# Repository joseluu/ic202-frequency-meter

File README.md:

# Fréquencemètre IC-202

Projet KiCad transcrit du schéma manuscrit, selon la description de
`docs/specifications.md`. Deux versions du schéma existent dans `docs/` :
`Schema.jpg`, la première photo, et `Schema_propre.jpg`, une reprise plus
lisible qui a servi à corriger plusieurs valeurs mal lues sur la première.

Chaîne de mesure : entrée RF → prédiviseur MB506 → étage de mise en forme à
transistor alimenté en 3 V → broche D5 d'un Arduino Pro Mini → afficheur LCD
3 digits 7 segments multiplexé, déporté au bout d'une nappe.

## Contenu

| Fichier | Rôle |
|---|---|
| `kicad/ic202-frequencemetre.kicad_pro` | Projet KiCad 10 |
| `kicad/ic202-frequencemetre.kicad_sch` | Schéma (feuille A3 unique) |
| `kicad/ic202-frequencemetre.kicad_pcb` | Carte, encore vide |
| `kicad/IC202.kicad_sym` | Symboles créés pour ce projet |
| `kicad/sym-lib-table` | Enregistrement de la bibliothèque de symboles `IC202` (portée projet) |
| `kicad/frequencemetre.pretty/` | Empreintes créées pour ce projet |
| `kicad/fp-lib-table` | Enregistrement de la bibliothèque d'empreintes `frequencemetre` (portée projet) |
| `kicad/ic202-frequencemetre.pdf` / `.svg` | Schéma exporté |
| `kicad/bom.csv` | Nomenclature |
| `kicad/erc.rpt` | Rapport ERC |
| `docs/Schema.jpg`, `docs/Schema_propre.jpg` | Schéma manuscrit d'origine et sa reprise lisible |
| `docs/LCD.png` | Fiche technique de l'afficheur LCD |

## État de vérification

- ERC : **0 erreur, 0 avertissement**.
- Netlist vérifiée broche à broche par export `kicadxml` après chaque retouche.
- `check_label_rotations.py` et `check_symbol_overlap.py` : OK.
- `lint_offgrid` : aucune coordonnée hors grille 1,27 mm.

## Organisation du schéma

La disposition reprend celle du schéma papier : alimentation en bandeau haut,
prédiviseur à gauche, mise en forme au centre, Arduino à droite, afficheur en
bas à droite. Les liaisons courtes à l'intérieur d'un bloc sont des fils ; les
rails d'alimentation et les signaux entre blocs passent par étiquettes de net.

## Règles de lisibilité appliquées

Les directives du skill
[kicad-schematic-readability](https://github.com/joseluu/kicad-schematic-readability)
sont respectées, et vérifiées par deux scripts locaux au poste de travail :

```
python check_label_rotations.py  .../ic202-frequencemetre.kicad_sch   # OK
python check_symbol_overlap.py   .../ic202-frequencemetre.kicad_sch   # OK
```

- **GND indépendants** : aucun fil de masse ne traverse la feuille, chaque
  composant a son propre stub GND.
- **Alimentation en haut, GND en bas** : les découplages ont leur broche
  positive vers le haut et leur masse vers le bas. Les connecteurs suivent la
  même règle : `J1` porte le +12 V en haut et la masse en bas, `J2` a son
  blindage dirigé vers le bas. Les deux ont été retournés par un miroir, ce qui
  inverse l'ordre des broches sans déplacer la broche de signal.
- **Signaux de gauche à droite** : entrée RF à gauche, progression vers
  l'Arduino puis l'afficheur à droite.
- **Étiquettes réservées aux signaux utiles** : rails, RF_IN, D5_SIG,
  VLCD_MID et les dix lignes LCD_COM/LCD_SEG. SW1 et SW2 sont marquées non
  connectées plutôt qu'étiquetées, faute d'utilité une fois flottantes.
- **Aucun chevauchement de symboles.**

### Placement des repères et valeurs

- **Circuits intégrés rectangulaires** (`U1`, `U2`, `U3`, `A1`, `DS1`) : repère
  et valeur au centre du rectangle, l'intérieur étant libre depuis le masquage
  des noms de broches. Ces champs ne portent aucun `justify`, le défaut centré
  étant celui recherché.
- **Résistances** : valeur au centre du corps et repère sur la ligne au-dessus,
  les deux suivant l'orientation du composant. Pour une résistance verticale le
  texte se lit de bas en haut, donc la ligne au-dessus est celle de gauche.
- **Condensateurs** : repère et valeur de part et d'autre du fil du symbole,
  juste sous les armatures. Le cas vertical exige un `justify` explicite, sinon
  le texte traverse le fil. Le cas horizontal sépare par la hauteur.

### Convention d'orientation des étiquettes

Une étiquette de net a besoin des **deux** informations, et elles doivent être
cohérentes entre elles :

- l'**angle** donne l'axe de lecture, et sert d'indicateur de direction pour le
  script de contrôle ;
- le **`justify`** décide de quel côté du point d'ancrage le texte est posé.
  C'est lui seul que KiCad utilise pour placer le texte.

| Angle | `justify` | Le texte se pose |
|---|---|---|
| 0 | `left bottom` | à droite de l'ancrage |
| 90 | `left bottom` | au-dessus |
| 180 | `right bottom` | à gauche |
| 270 | `right bottom` | en dessous |

Le second mot `bottom` décale le texte perpendiculairement, pour qu'il ne soit
pas posé sur le fil.

**Piège n° 1 : pas de `justify` du tout.** Le défaut de KiCad est *centré*, donc
l'étiquette chevauche son propre point de connexion et le numéro de broche.
C'est visible surtout sur les étiquettes posées directement sur une broche, les
étiquettes en bout de stub ayant de la place autour. Chaque étiquette doit
porter un `justify` explicite.

**Piège n° 2 : `lint_schematic_cosmetic` passe `orient_labels`.** Cette passe du
serveur MCP produit une orientation à 180° de la bonne. Ne pas la relancer sur
ce schéma. Si c'est fait par erreur, réappliquer la table ci-dessus.

**Autre piège.** Dans un champ `property` d'un symbole tourné à 90°, l'angle
est relatif au symbole : il faut écrire 270 pour obtenir un texte horizontal.
C'est le cas des repères de `R7`..`R16`.

### Alimentation

`J1` (+12 V) → `U1` AMS1117-5.0 → +5 V → `U2` AMS1117 (ADJ) → +3 V.
Découplage 100 nF + 10 µF sur chacun des trois rails.

Les deux régulateurs sont en boîtier CMS SOT-223, choisis dans le stock
PartsBox de l'utilisateur plutôt que les L7805/LM317L d'origine (traversants,
non tenus en stock CMS) : mêmes coordonnées de broches, seule leur
numérotation change. Sur `U1`, l'entrée devient la broche 3 (VI) et la
sortie la broche 2 (VO) — sur `U2`, `1`=ADJ, `2`=VO, `3`=VI comme
auparavant, l'architecture (référence 1,25 V, pont diviseur) étant la même
famille que le LM317.

Le +3 V est réglé par `R1` (220 R, VO→ADJ de `U2`) et `R2` (300 R,
ADJ→GND) :

    Vout = 1,25 x (1 + 300/220) = 2,95 V

C'est proche de la tension de service du LCD (3,0 V), indiquée sur sa fiche.
Ce pont n'a pas changé de valeur : l'AMS1117 ajustable utilise la même
référence 1,25 V que le LM317L qu'il remplace.

`#FLG01` et `#FLG02` sont les PWR_FLAG des rails +12 V et GND, qui ne sont
alimentés que par un connecteur.

`J1` est un connecteur 4 broches (header 2,54 mm) : les broches 1 et 2,
adjacentes, portent toutes deux le +12 V ; les broches 3 et 4, adjacentes,
portent toutes deux le GND. Le doublement de chaque broche répartit le
courant d'alimentation sur deux points de contact.

### Prédiviseur MB506

`U3` est le Fujitsu **MB506PF**, boîtier CMS SOP-8 (208 mil, empreinte
`Package_SO:SOIC-8_5.3x6.2mm_P1.27mm`), en remplacement du MB506 traversant
DIP-8 d'origine — même brochage 1-8 (IN, VCC, SW1, OUT, GND, SW2, NC, /IN),
choisi dans le stock PartsBox de l'utilisateur.

- `J2` entrée RF, terminaison `R3` 51 R, liaison capacitive `C7` 1 nF vers IN (broche 1).
  Pas de connecteur SMA monté : un mini câble coaxial est soudé directement
  sur deux pastilles (`TestPoint:TestPoint_2Pads_Pitch2.54mm_Drill0.8mm`,
  pas 2,54 mm, perçage 0,8 mm) — âme sur la pastille 1 (IN), blindage sur
  la pastille 2 (GND).
- Entrée complémentaire /IN (broche 8) : découplée à la masse par `C8` 100 nF,
  et polarisée par `R20` 470 kΩ vers GND. C'est le réseau optionnel repéré sur
  le schéma relu (voir « Hypothèses de transcription ») ; il fixe le point de
  repos de l'entrée complémentaire quand le MB506 est piloté en simple
  extrémité (un seul signal sur IN, ~IN laissée au repos).
- VCC (broche 2) en +5 V, découplé par `C9` 100 nF.
- Sortie OUT (broche 4) : pull-down `R19` (2K2) vers GND, en parallèle de la
  liaison capacitive vers l'étage de mise en forme. C'est une terminaison
  usuelle pour une sortie de type collecteur ouvert / ECL.
- Broche 7 (NC) marquée non connectée. La datasheet Fujitsu ne lui donne
  aucune fonction : le rapport de division est fixé uniquement par SW1 et
  SW2, il n'y a pas de troisième entrée de sélection.
- SW1 (broche 3) et SW2 (broche 6) reliées au rail +5 V **à travers un
  cavalier à souder fermé** (`JP11` sur `MB506_SW1`, `JP12` sur `MB506_SW2`,
  empreinte `Jumper:SolderJumper-2_P1.3mm_Bridged_Pad1.0x1.5mm`).

D'après la table du constructeur (H = VCC, L = ouvert), SW1 et SW2 au niveau H
donnent le rapport **1/64**, comportement par défaut de cette carte :

| SW1 | SW2 | Division |
|---|---|---|
| ouvert | ouvert | 1/256 |
| ouvert | +5 V | 1/128 |
| +5 V | ouvert | 1/128 |
| **+5 V** | **+5 V** | **1/64** |

Le schéma d'origine prévoyait un connecteur `J3` pour choisir le rapport ; il
n'apparaît plus sur le schéma relu, qui laisse SW1/SW2 flottants (1/256 par
défaut). À la demande explicite, les deux broches sont ici reliées au +5 V
pour fixer la division à 1/64. `JP11`/`JP12` remplacent ce sélecteur : livrés
fermés, ils conservent le 1/64 ; couper `JP11` **ou** `JP12` au cutter remet
la broche correspondante en l'air (niveau L) et donne 1/128, couper les deux
donne 1/256. Un coup de fer à souder revient en arrière.

### Mise en forme vers D5

`Q1` est le NPN RF **2SC5551AE-TD-E** (onsemi), boîtier CMS SOT-89
(30 V, 300 mA, fT = 3,5 GHz), en remplacement du 2N2369 traversant (TO-18,
fT ≈ 500 MHz) — choisi dans le stock PartsBox de l'utilisateur, largement
assez rapide pour ce rôle. Le brochage réel (1 = base, 2 = collecteur sur
la languette, 3 = émetteur) ne correspond pas à l'ordre du symbole générique
KiCad `Q_NPN_BEC` (broche 2 = émetteur, broche 3 = collecteur) : le symbole a
donc été remplacé par `Q_NPN_BCE` (broche 2 = collecteur, broche 3 =
émetteur), qui a la même géométrie de broches — seul l'étiquetage
broche/fonction change, le câblage existant reste intact — pour que la
numérotation corresponde à celle de l'empreinte SOT-89.

Sortie ECL du MB506 → `C10` 100 nF → base de `Q1`. `R4` 3,3 kΩ relie
la base au collecteur (contre-réaction continue, pas une résistance série vers
la masse comme dans une première version du schéma). Émetteur à la masse,
collecteur tiré au +3 V par `R6` 470 Ω, et c'est ce nœud collecteur qui attaque
D5. Le point de repos de `Q1` s'auto-régule par cette contre-réaction plutôt
que par un pont de base classique. Le niveau logique vu par l'Arduino est donc
bien du 3 V, d'où la présence du second régulateur (`U2`).

### Arduino

L'Arduino Pro Mini est la version **3,3 V / 8 MHz**, alimentée sur sa broche VCC
depuis le rail +3 V (le régulateur de la carte est contourné, RAW non connectée).
L'ATmega328P à 8 MHz fonctionne sans réserve jusqu'à 2,7 V.

D13 est laissé libre à cause de la LED intégrée. TXO/RXI restent disponibles
pour la programmation par le connecteur FTDI de la carte.

**Montage sur picots.** Le Pro Mini n'est pas soudé directement : il se
branche sur deux barrettes de picots femelles soudées sur le PCB principal
(empreinte `frequencemetre:Arduino_Pro_Mini_Header_2x12`). Il se trouve donc surélevé
par rapport à la carte, et le volume dégagé en dessous est disponible pour
d'autres composants. Cette empreinte ne modélise que les deux courtyards des
barrettes (pas de contour de carte complet ni de courtyard unique englobant
tout le module), justement pour ne pas signaler ce volume comme occupé.

Géométrie vérifiée contre l'empreinte open source
[`Arduino_Pro_Mini_Socket`](https://github.com/Alarm-Siren/arduino-kicad-library)
(2 rangées de 12 broches au pas de 2,54 mm, 15,24 mm entre rangées) : 24
broches au total, pas de connecteur de programmation FTDI modélisé. Les
broches A4/SDA et A5/SCL du Pro Mini réel ne sont pas sur ces barrettes — ce
sont des pastilles au dos du module, atteignables seulement par un fil volant
— et ont été retirées du symbole `IC202:Arduino_Pro_Mini`, qui ne comptait
d'ailleurs déjà aucune connexion sur ces deux broches.

### Afficheur LCD

`docs/LCD.png` donne la fiche du composant :

| Caractéristique | Valeur |
|---|---|
| Technologie | TN, polariseur réflectif positif |
| Multiplexage | 1/4 duty, 1/2 bias |
| Tension de service | 3,0 V |
| Angle de lecture | 6 heures |
| Broches | 10, au pas de 2,00 mm |

Référence commerciale :
<https://fr.aliexpress.com/item/1005003745628043.html>

Le 1/4 duty impose **4 communs**, et les 10 broches se répartissent donc en
4 communs plus **6 segments**. Cela adresse 4 × 6 = 24 segments, dont 21 pour
les trois chiffres.

C'est un afficheur à cristaux liquides : il ne consomme aucun courant et ne
supporte pas de tension continue permanente, qui le détruirait par
électrolyse. Il n'y a donc **pas de résistance de limitation** ; l'attaque se
fait en alternatif, par inversion de polarité à chaque trame.

**Attaque en 1/2 bias par tri-état.** Chaque ligne a besoin de trois niveaux :
0 V, 1,5 V et 3 V. Les broches de l'Arduino en fournissent deux, et le
troisième vient de la mise en haute impédance : la ligne rejoint alors la
référence à mi-tension `VLCD_MID` à travers sa résistance de 100 kΩ.

| Élément | Rôle |
|---|---|
| `R7`..`R16` (100 kΩ) | une par ligne, vers `VLCD_MID` |
| `R17`, `R18` (10 kΩ) | pont générant `VLCD_MID` = 3 V / 2 |
| `C12` (1 µF) | découplage de la référence |

Le pont est dix fois plus raide que les résistances de ligne, pour que la
référence ne bouge pas quand plusieurs broches commutent.

**Cavaliers de coupure devant `J4`.** Un cavalier à souder fermé par défaut
(`JP1`..`JP10`, empreinte `Jumper:SolderJumper-2_P1.3mm_Bridged_Pad1.0x1.5mm`)
est inséré en série entre chaque ligne (`R7`..`R16`) et sa broche de `J4` —
un par ligne LCD. Chaque ligne passe donc par deux nœuds électriques
distincts : le nœud côté Arduino/résistance (nom de net inchangé,
`LCD_COM1`..`LCD_SEG6`) et le nœud côté `J4` (nommé explicitement
`J4_COM1`..`J4_SEG6`), reliés par le cavalier. Fermés (comportement par
défaut, pont de cuivre déjà présent sur l'empreinte), la liaison vers la
nappe LCD est normale ; les couper au cutter isole la carte de la nappe —
utile pour tester l'étage Arduino/résistances seul avant de raccorder
l'afficheur. Un coup de fer à souder rétablit ensuite la liaison.

**Deux bugs de câblage trouvés et corrigés après coup, à l'occasion d'une
tentative de routage** (voir plus bas) :

1. Les 10 fils reliant chaque cavalier à sa broche de `J4` passaient par un
   point de coude intermédiaire à une abscisse commune (`x=330.2`) pour
   rester orthogonaux. Plusieurs de ces segments verticaux se chevauchaient
   partiellement sur cette même abscisse (les nappes de lignes LCD ont des
   pas différents côté résistances — 5,08 mm — et côté `J4` — 2,54 mm — donc
   leurs coudes intermédiaires ne tombent pas aux mêmes hauteurs), ce qui a
   **court-circuité entre elles plusieurs lignes LCD** (`COM2`-`COM3`-`COM4`-`SEG1`
   d'un côté, `SEG3`-`SEG4` de l'autre). L'ERC ne signalait qu'un avertissement
   discret (« multiple_net_names »), pas une erreur — c'est une relecture du
   netlist exporté par `kicad-cli` (source de vérité) qui a révélé l'ampleur
   réelle du problème. Corrigé en remplaçant les 10 chemins coudés par un
   fil diagonal unique par ligne (pas de point partagé entre lignes
   différentes, donc aucun risque de chevauchement accidentel).
2. Après correction du point 1, le nom de net explicite (`J4_COM1` etc.) a
   dû être ajouté sur chaque broche de `J4` : sans lui, `sync_schematic_to_board`
   (l'outil MCP qui importe le schéma dans le PCB) n'arrivait pas à
   résoudre les nets anonymes auto-générés par KiCad (`Net-(J4-Pin_X)`) et
   laissait ces broches et celles des cavaliers **sans net du tout** côté
   PCB — invisibles pour le ratsnest et l'autorouteur, silencieusement, sans
   qu'aucun outil ne le signale comme une erreur. Un nom de net explicite
   sur chaque broche contourne cette limite.

**Affectation des broches de l'Arduino :**

| Broche | Ligne LCD |
|---|---|
| D5 | entrée de comptage depuis l'étage transistor |
| D2, D3, D4, D6 | COM1, COM2, COM3, COM4 |
| D7, D8, D9, D10, D11, D12 | SEG1 à SEG6 |

**Liaison par nappe.** Le LCD est déporté au bout d'une nappe de 10
conducteurs. `J4` (header mâle au pas de 2,54 mm) est le seul connecteur
présent sur la carte ; `DS1`, l'afficheur, n'est **pas monté sur ce PCB**,
il se trouve à l'autre extrémité du câble. Le symbole `DS1` est marqué
« hors carte » (`on_board: no`) : il reste dans le schéma et la nomenclature
pour documenter le système complet, mais `sync_schematic_to_board` ne lui
crée pas d'empreinte sur cette carte.

## Intention de conception pour le placement/routage

Le schéma porte, en plus de la connectivité, une propriété masquée
`Placement` sur chaque composant dont la position physique finale importe
au-delà du simple raccordement électrique — suivant le skill Claude Code
`conception-electronique-kicad`. Cette propriété n'apparaît pas sur le
schéma ; elle se lit via `get_schematic_component` ou en filtrant le
`.kicad_sch` sur `(property "Placement"`. **Elle ne s'applique pas toute
seule** : au moment du placement/routage, il faut demander explicitement de
la respecter.

**Découplage documenté** (préfixe `LOCAL`) :

| Réf. | Rôle |
|---|---|
| `C1`, `C2` | HF / bulk BF, entrée `J1` et broche 3 (VI) de `U1` |
| `C3`, `C4` | HF / bulk BF, nœud +5 V partagé broche 2 (VO) de `U1` / broche 3 (VI) de `U2` |
| `C5`, `C6` | HF / bulk BF, broche VO (sortie) de `U2` |
| `C9` | HF, broche VCC de `U3` |
| `C8` | HF de la broche ~IN (signal, pas alimentation) de `U3`, avec `R20` |
| `C11` | HF du rail +3 V près de `R6`, point le plus éloigné de `U2` |
| `C12` | référence `VLCD_MID`, point milieu du pont `R17`/`R18` |

Vérification faite : les trois circuits intégrés actifs (`U1`, `U2`, `U3`)
ont chacun un découplage local documenté sur leur(s) broche(s)
d'alimentation. `A1` (Arduino Pro Mini) n'est pas inclus dans cette
vérification : c'est un module complet avec son propre découplage embarqué,
pas un CI nu à décrire ici.

**Boucles critiques documentées** (préfixe `LOOP CRITIQUE`, hors
découplage) :

- `J2`-`R3`-`C7` → broche IN de `U3` : chemin RF d'entrée, jusqu'à 2,4 GHz,
  surface minimale impérative.
- `U3`(OUT)-`R19`-`C10`-`R4`-`R6`-`Q1` → `D5_SIG` (broche D5 de `A1`) : chemin
  de comptage, le signal que l'instrument existe pour mesurer — à éloigner
  des sources de bruit.

### Placement initial (fait)

Carte **80 × 50 mm**, paysage (hauteur réduite de 70 à 50 mm après le
passage aux boîtiers CMS ci-dessous, qui a libéré de la place). Emplacements
imposés par l'utilisateur :

- `J1` (+12 V IN) : bord haut, au milieu, rangée de broches **parallèle**
  au bord (rotation 90° par rapport à l'orientation par défaut du
  footprint, qui les mettait perpendiculaires).
- `J2` (RF IN, coax à souder) : bord gauche, rangée de broches parallèle au
  bord (même correction de rotation).
- `J4` (nappe LCD, header 2,54 mm) : bord droit.
- `A1` (Arduino Pro Mini sur picots) : décalé de 3 mm vers la gauche par
  rapport au premier placement, toujours à droite et proche de `J4`,
  orientation paysage, extrémité USB/FTDI côté gauche (rotation 90°, vérifiée
  par la mesure des pads comme au premier placement).
- `R7`..`R16` (échelle de polarisation LCD) : **sous `A1`**, dans le volume
  dégagé entre les deux barrettes de picots — l'empreinte de `A1` ne porte
  que les deux courtyards des barrettes (voir « Arduino » ci-dessus), donc
  cet espace n'est pas signalé occupé.

L'orientation « parallèle au bord le plus proche » pour `J1`/`J2` est
désormais une règle par défaut du skill `kicad-pcb-placement` : elle
s'applique à tout connecteur proche d'un bord, sauf orientation contraire
explicitement demandée.

Le reste (bloc d'alimentation, chaîne RF/prédiviseur, chemin de comptage,
cavaliers `JP1`-`JP10`, `R17`/`R18`/`C12`) est réparti par proximité en
suivant les groupes `Placement` du schéma. Vérifié via `run_drc`
(kicad-cli, source de vérité du projet) : **0 erreur**, 3 avertissements
cosmétiques silkscreen. Méthode suivie : skill Claude Code
`kicad-pcb-placement`.

### Routage (fait)

Autoroutage via Freerouting (`autoroute`, 2 couches F.Cu/B.Cu) sur ce
placement : **16,5 s**, 278 pistes + 29 vias. Deux passes de nettoyage
après coup :

- 11 pistes exportées à 0,15 mm par le pipeline KiCad→DSN→Freerouting alors
  que la carte impose 0,2 mm minimum (limite connue de ce pipeline,
  reproductible même en relançant l'autoroutage plusieurs fois de suite —
  ne se corrige pas tout seul). Corrigées une par une : piste supprimée puis
  retracée au même endroit avec une largeur explicite de 0,2 mm.
- Un essai de placement alternatif via l'outil externe **FD-Autoplacer**
  (`github.com/joseluu/FD-Autoplacer`, optimisation par descente de
  gradient) a été comparé sur ce même schéma : passage clone → exécution →
  import direct, sans succès retenu (chevauchement de courtyard réel,
  plusieurs composants débordant du bord de carte) — le placement à la main
  ci-dessus a été conservé.

Résultat final vérifié via `run_drc` : **0 erreur**, 10 avertissements
cosmétiques (7 vias non connectées des deux côtés, 1 chevauchement
silkscreen, 2 silkscreen sur cuivre).

### Bug critique trouvé et corrigé après coup : broches actives sans net

En inspectant le PCB routé, une broche visiblement connectée à trop
d'endroits (broche 1 de `U3`) a révélé un bug bien plus large : **5 nets
sans label explicite** (`Net-(U3-IN)`, `Net-(U3-OUT)`, `Net-(U3-~{IN})`,
`Net-(Q1-B)`, `Net-(U2-ADJ)`) — électriquement valides au niveau du schéma,
l'ERC ne signale rien — mais que `sync_schematic_to_board` échoue à
résoudre silencieusement, laissant les broches concernées **sans net du
tout côté PCB**. Conséquence réelle : la sortie du prescaler (`U3` OUT) et
la base de `Q1` n'ont jamais été reliées à la chaîne de comptage, sur les
deux cartes, malgré un DRC à 0 erreur — une broche sans net n'ayant par
ailleurs aucune obligation de clearance, ce qui explique l'apparence de
connexion multiple constatée.

Corrigé : les 5 nets renommés explicitement (`MB506_IN`, `MB506_OUT`,
`MB506_NIN`, `Q1_BASE`, `U2_ADJ`), resynchronisés vers les deux PCB, la
règle de clearance globale remontée de 0 mm (!) à 0,2 mm — qui a d'ailleurs
mis au jour des croisements de pistes que le clearance nul masquait — puis
carte principale entièrement reroutée : **0 erreur `run_drc`** au final
(327 pistes, 40 vias, même limite de 0,15 mm sur quelques pistes corrigée
comme précédemment). Règle ajoutée au skill `conception-electronique-kicad`
pour détecter ce cas systématiquement avant tout premier routage.

**Piège outil découvert à cette occasion :** `check_courtyard_overlaps`
(MCP) évalue le chevauchement de courtyard d'une empreinte à partir de sa
*bounding box globale*, pas des polygones réels — pour une empreinte à
plusieurs rectangles de courtyard disjoints comme celle de `A1` (justement
conçue pour laisser un volume libre au milieu), l'outil signale à tort un
chevauchement dès qu'un autre composant entre dans cette bounding box, y
compris pile au centre du volume libre. Vérifié en plaçant une résistance
au centre exact de `A1` et en comparant : `check_courtyard_overlaps` la
signale en conflit, `run_drc` (qui lit les vrais polygones KiCad) ne
signale rien. Pour toute empreinte de ce genre, se fier à `run_drc`, pas à
`check_courtyard_overlaps`.

## Hypothèses de transcription

La photo du schéma manuscrit n'est pas assez nette pour toutes les annotations.
Les points suivants ont été déduits ; ils sont à confronter à l'original.

| Élément | Retenu | Raison |
|---|---|---|
| `Q1` | 2N2369 | Lecture la plus probable de l'annotation ; transistor de commutation rapide cohérent avec l'usage. Tout NPN rapide équivalent convient. |
| `R17`, `R18` | 3,3 kΩ chacune | Valeur clairement lisible sur le schéma relu. |
| Affectation des 10 broches de `DS1` | 1..4 = COM1..COM4, 5..10 = SEG1..SEG6 | La fiche donne le nombre de broches et le multiplexage, pas leur ordre. **À confirmer avant fabrication.** |

Le schéma manuscrit relu (`docs/Schema_propre.jpg`) est nettement plus lisible
que la première photo et a permis de corriger plusieurs valeurs mal lues, ainsi
que d'ajouter des composants absents de la première transcription. Le tableau
ci-dessous liste les changements :

| Élément | Ancienne valeur | Valeur corrigée |
|---|---|---|
| `R1` | 100 R | 220 R |
| `R2` | 160 R | 300 R |
| `R6` | 1 k | 470 R |
| `C8` | 1 n | 100 n |
| `R17`, `R18` | 10 k | 3,3 k |
| ancien `R5` (100 k, base→GND) | présent | supprimé, absent du schéma relu |
| ancien `J3` (sélecteur SW1/SW2) | présent | supprimé, remplacé par les cavaliers `JP11`/`JP12` (fermés = 1/64) |
| `R19` (2K2, OUT MB506→GND) | absent | ajouté |
| `R4` | 1 k, en série cap→base | 3,3 k, en contre-réaction base→collecteur |
| `R20` (470 kΩ, broche 8 ~IN→GND) | absent | ajouté |

Deux de ces corrections ont été apportées directement dans KiCad par
l'utilisateur puis relues par la suite : le rebranchement de `R4` en
contre-réaction base→collecteur (la première transcription le plaçait par
erreur en série entre `C10` et la base), et l'ajout de `R20`, le réseau
repéré près de la broche complémentaire (~IN, broche 8) du MB506, qui polarise
cette broche vers la masse quand le composant est piloté en entrée simple.

## Ce qui reste à faire

1. **Obtenir la table de correspondance segments du LCD**, c'est-à-dire quel
   couple (COM, SEG) allume quel segment de quel chiffre. Elle n'est pas dans
   la fiche et conditionne le firmware. Sans elle, on peut router la carte mais
   pas afficher un chiffre juste.
2. **Confirmer l'affectation des 10 broches** en communs et segments.
3. **Empreinte de `A1`.** `DS1` n'a pas besoin d'empreinte, il n'est pas
   monté sur ce PCB (voir « Afficheur LCD »). `J4` est un header 1×10 au
   pas de 2,54 mm (`Connector_PinHeader_2.54mm:
   PinHeader_1x10_P2.54mm_Vertical`).
4. **Confirmer les valeurs du tableau d'hypothèses** sur le schéma d'origine.
5. ~~Routage de la carte~~ — fait (voir « Routage » ci-dessus), 0 erreur DRC.
6. **Firmware.** Comptage sur D5, division par 256 à compenser, puis génération
   des trames LCD en 1/4 duty et 1/2 bias : chaque broche prend tour à tour
   l'état haut, bas ou haute impédance, et la polarité s'inverse à chaque trame
   pour que la tension moyenne sur chaque segment reste nulle.

## Ouvrir le projet

```
"C:/Program Files/KiCad/10.0/bin/kicad.exe" kicad/ic202-frequencemetre.kicad_pro
```

La bibliothèque `IC202` est enregistrée en portée projet ; elle est trouvée
automatiquement à l'ouverture.

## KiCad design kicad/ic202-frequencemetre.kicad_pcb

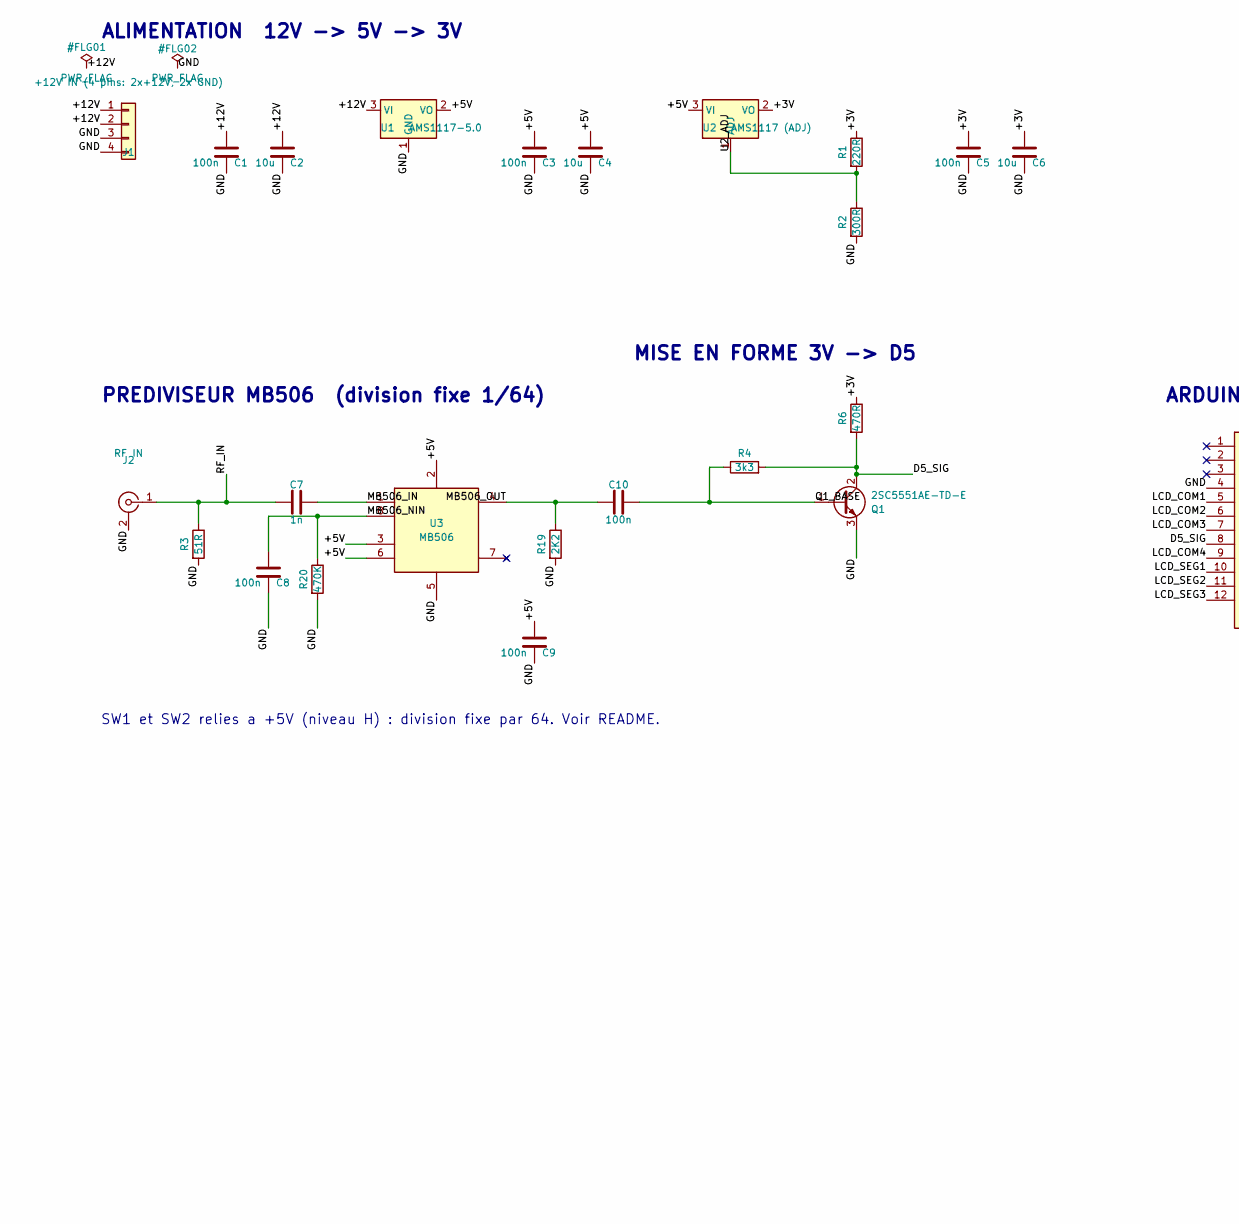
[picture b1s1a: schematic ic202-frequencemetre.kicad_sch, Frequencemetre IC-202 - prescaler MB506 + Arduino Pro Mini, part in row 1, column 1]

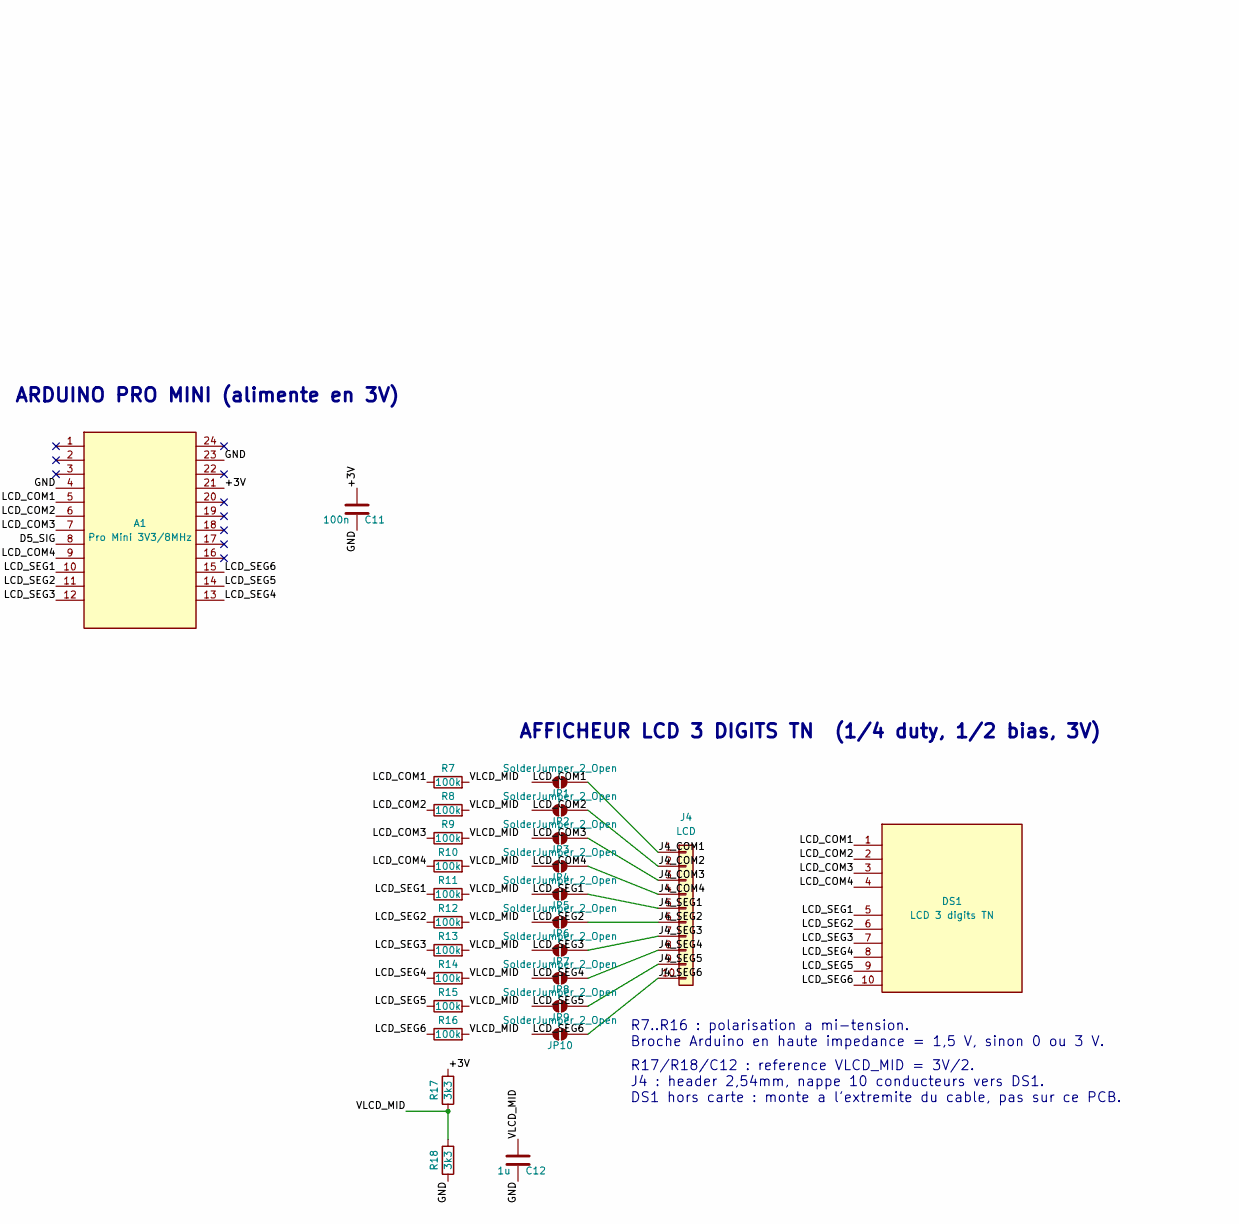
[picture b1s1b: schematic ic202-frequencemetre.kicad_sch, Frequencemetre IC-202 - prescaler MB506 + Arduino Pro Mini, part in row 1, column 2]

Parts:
A1: Pro Mini 3V3/8MHz; Arduino_Pro_Mini_Header_2x12
C1, C3, C5, C8, C9, C10, C11: 100n; C_0603_1608Metric
C2, C4, C6: 10u; C_0805_2012Metric
C7: 1n; C_0603_1608Metric
C12: 1u; C_0805_2012Metric
DS1: LCD 3 digits TN
J1: +12V IN (4 pins: 2x+12V, 2x GND); PinHeader_1x04_P2.54mm_Vertical
J2: RF IN; TestPoint_2Pads_Pitch2.54mm_Drill0.8mm
J4: LCD; PinHeader_1x10_P2.54mm_Vertical
JP1, JP2, JP3, JP4, JP5, JP6, JP7, JP8, JP9, JP10: SolderJumper_2_Open; SolderJumper-2_P1.3mm_Open_Pad1.0x1.5mm
Q1: 2SC5551AE-TD-E; SOT-89-3
R1: 220R; R_0603_1608Metric
R2: 300R; R_0603_1608Metric
R3: 51R; R_0603_1608Metric
R4, R17, R18: 3k3; R_0603_1608Metric
R6: 470R; R_0603_1608Metric
R7, R8, R9, R10, R11, R12, R13, R14, R15, R16: 100k; R_0603_1608Metric
R19: 2K2; R_0603_1608Metric
R20: 470K; R_0603_1608Metric
U1: AMS1117-5.0; SOT-223-3_TabPin2
U2: AMS1117 (ADJ); SOT-223-3_TabPin2
U3: MB506; SOIC-8_5.3x6.2mm_P1.27mm

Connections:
+3V: A1.21 (VCC), C5.1, C6.1, C11.1, R1.1, R6.1, R17.1, U2.2 (VO)
+5V: C3.1, C4.1, C9.1, U1.2 (VO), U2.3 (VI), U3.2 (VCC), U3.3 (SW1), U3.6 (SW2)
+12V: C1.1, C2.1, J1.1, J1.2, U1.3 (VI)
D5_SIG: A1.8 (D5), Q1.2 (C), R4.2, R6.2
GND: A1.4 (GND), A1.23 (GND2), C1.2, C2.2, C3.2, C4.2, C5.2, C6.2, C8.2, C9.2, C11.2, C12.2, J1.3, J1.4, J2.2 (Ext), Q1.3 (E), R2.2, R3.2, R18.2, R19.2, R20.2, U1.1 (GND), U3.5 (GND)
J4_COM1: J4.1, JP1.2 (B)
J4_COM2: J4.2, JP2.2 (B)
J4_COM3: J4.3, JP3.2 (B)
J4_COM4: J4.4, JP4.2 (B)
J4_SEG1: J4.5, JP5.2 (B)
J4_SEG2: J4.6, JP6.2 (B)
J4_SEG3: J4.7, JP7.2 (B)
J4_SEG4: J4.8, JP8.2 (B)
J4_SEG5: J4.9, JP9.2 (B)
J4_SEG6: J4.10, JP10.2 (B)
LCD_COM1: A1.5 (D2), DS1.1 (COM1), JP1.1 (A), R7.1
LCD_COM2: A1.6 (D3), DS1.2 (COM2), JP2.1 (A), R8.1
LCD_COM3: A1.7 (D4), DS1.3 (COM3), JP3.1 (A), R9.1
LCD_COM4: A1.9 (D6), DS1.4 (COM4), JP4.1 (A), R10.1
LCD_SEG1: A1.10 (D7), DS1.5 (SEG1), JP5.1 (A), R11.1
LCD_SEG2: A1.11 (D8), DS1.6 (SEG2), JP6.1 (A), R12.1
LCD_SEG3: A1.12 (D9), DS1.7 (SEG3), JP7.1 (A), R13.1
LCD_SEG4: A1.13 (D10), DS1.8 (SEG4), JP8.1 (A), R14.1
LCD_SEG5: A1.14 (D11), DS1.9 (SEG5), JP9.1 (A), R15.1
LCD_SEG6: A1.15 (D12), DS1.10 (SEG6), JP10.1 (A), R16.1
MB506_IN: C7.2, U3.1 (IN)
MB506_NIN: C8.1, R20.1, U3.8 (~IN)
MB506_OUT: C10.1, R19.1, U3.4 (OUT)
Q1_BASE: C10.2, Q1.1 (B), R4.1
RF_IN: C7.1, J2.1 (In), R3.1
U2_ADJ: R1.2, R2.1, U2.1 (ADJ)
VLCD_MID: C12.1, R7.2, R8.2, R9.2, R10.2, R11.2, R12.2, R13.2, R14.2, R15.2, R16.2, R17.2, R18.1

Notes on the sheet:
PREDIVISEUR MB506 (division fixe 1/64)
SW1 et SW2 relies a +5V (niveau H) : division fixe par 64. Voir README.
AFFICHEUR LCD 3 DIGITS TN (1/4 duty, 1/2 bias, 3V)
ARDUINO PRO MINI (alimente en 3V)
ALIMENTATION 12V -> 5V -> 3V
MISE EN FORME 3V -> D5
R17/R18/C12 : reference VLCD_MID = 3V/2. J4 : header 2,54mm, nappe 10 conducteurs vers DS1. DS1 hors carte : monte a l'extremite du cable, pas sur ce PCB.
R7..R16 : polarisation a mi-tension. Broche Arduino en haute impedance = 1,5 V, sinon 0 ou 3 V.

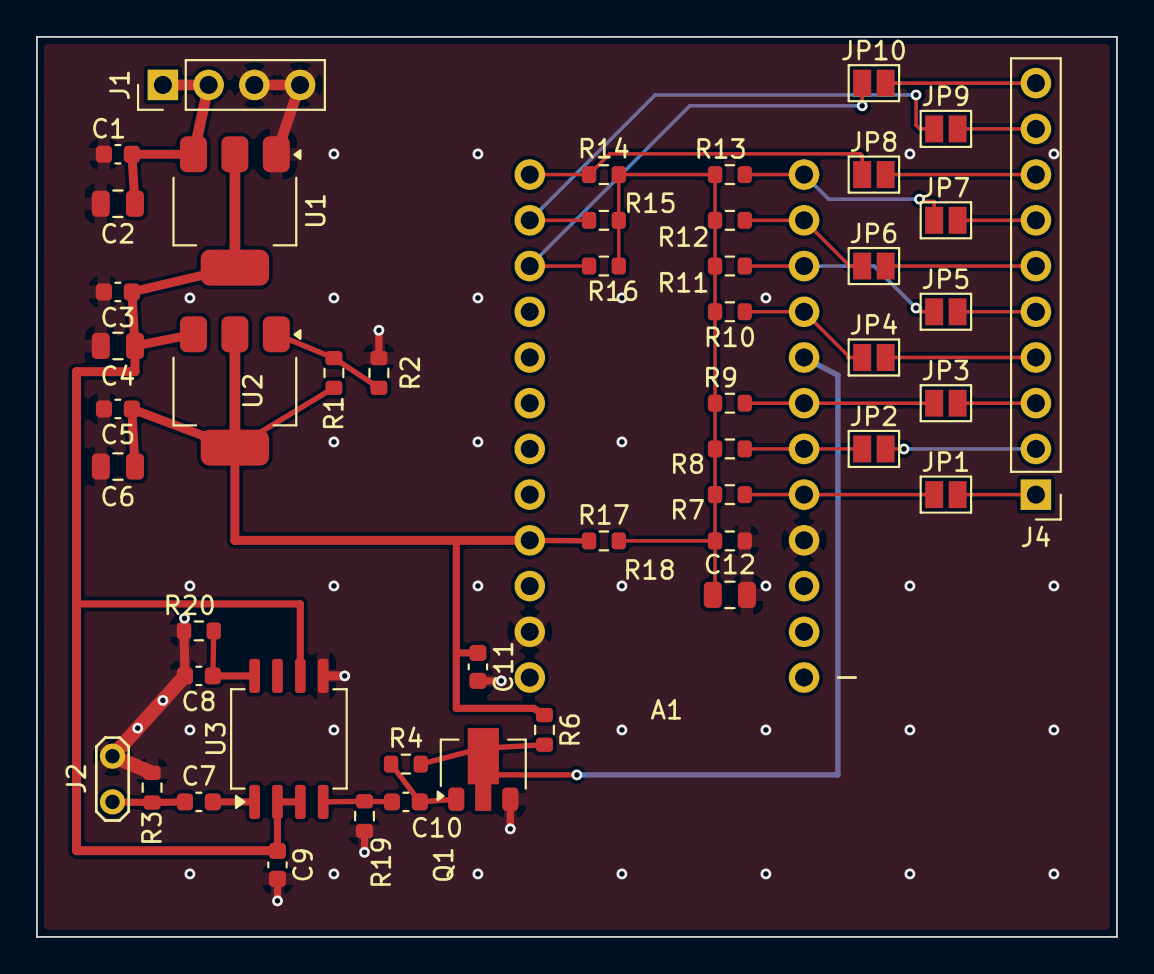
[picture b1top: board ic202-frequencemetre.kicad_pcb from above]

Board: 2 copper layers, 60.0 x 50.0 mm, 49 parts (0 on the bottom side), 32 nets.

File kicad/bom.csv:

"Reference","Value","Footprint","Description"
"A1","Pro Mini 3V3/8MHz","frequencemetre:Arduino_Pro_Mini_Header_2x12","Arduino Pro Mini module (ATmega328P), 2x12 pin headers. A4/SDA et A5/SCL (broches arriere, non alignees sur les headers) omises : non utilisees dans ce projet."
"C1,C3,C5,C8-C11","100n","Capacitor_SMD:C_0603_1608Metric","Unpolarized capacitor"
"C2,C4,C6","10u","Capacitor_SMD:C_0805_2012Metric","Unpolarized capacitor"
"C7","1n","Capacitor_SMD:C_0603_1608Metric","Unpolarized capacitor"
"C12","1u","Capacitor_SMD:C_0805_2012Metric","Unpolarized capacitor"
"DS1","LCD 3 digits TN","","Afficheur LCD TN 3 digits 7 segments, 10 broches, multiplexe 1/4 duty 1/2 bias, 3.0V. Repartition COM/SEG a confirmer aupres du fournisseur."
"J1","+12V IN (4 pins: 2x+12V, 2x GND)","Connector_PinHeader_2.54mm:PinHeader_1x04_P2.54mm_Vertical","Connecteur 4 pins, paires adjacentes : pins 1-2 = +12V, pins 3-4 = GND"
"J2","RF IN","TestPoint:TestPoint_2Pads_Pitch2.54mm_Drill0.8mm","coaxial connector (BNC, SMA, SMB, SMC, Cinch/RCA, LEMO, ...)"
"J4","LCD","Connector_PinHeader_2.54mm:PinHeader_1x10_P2.54mm_Vertical","Generic connector, single row, 01x10, script generated (kicad-library-utils/schlib/autogen/connector/)"
"JP1-JP10","SolderJumper_2_Open","Jumper:SolderJumper-2_P1.3mm_Open_Pad1.0x1.5mm","Solder Jumper, 2-pole, open"
"Q1","2SC5551AE-TD-E","Package_TO_SOT_SMD:SOT-89-3","onsemi 2SC5551A, NPN RF transistor 30V 300mA fT=3.5GHz, SOT-89 (pin1=B, pin2/tab=C, pin3=E)"
"R1","220R","Resistor_SMD:R_0603_1608Metric","Resistor"
"R2","300R","Resistor_SMD:R_0603_1608Metric","Resistor"
"R3","51R","Resistor_SMD:R_0603_1608Metric","Resistor"
"R4,R17,R18","3k3","Resistor_SMD:R_0603_1608Metric","Resistor"
"R6","470R","Resistor_SMD:R_0603_1608Metric","Resistor"
"R7-R16","100k","Resistor_SMD:R_0603_1608Metric","Resistor"
"R19","2K2","Resistor_SMD:R_0603_1608Metric","Resistor"
"R20","470K","Resistor_SMD:R_0603_1608Metric","Resistor"
"U1","AMS1117-5.0","Package_TO_SOT_SMD:SOT-223-3_TabPin2","1A LDO regulator, fixed output 5.0V, SOT-223"
"U2","AMS1117 (ADJ)","Package_TO_SOT_SMD:SOT-223-3_TabPin2","1A LDO regulator, adjustable output, SOT-223"
"U3","MB506","Package_SO:SOIC-8_5.3x6.2mm_P1.27mm","Fujitsu MB506PF ultra high frequency prescaler, 2.4 GHz, divide by 64/128/256, SOP-8 (208mil)"
